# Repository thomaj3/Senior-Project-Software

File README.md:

This is the software for the Senior Project Curve Tracer utulizing PSoC

This curve tracer can handle enhancement mode NMOS and PMOS, as well as NPN and PNP BJTs

Value | Transistor Type | Range | Unit |
| --- | --- | --- | --- |
Id | N,P | [0, 20] | mA |
Ic | N,P | [0, 20] | mA |
Vd | N,P | [0, 9] | V |
Vc | N,P | [0, 9] | V |
Vg | N | [0, 4] | V |
Vg | P | [5, 9] | V |
Ib | N | [0 100] | uA |
Ib | P | [0 100] | uA |

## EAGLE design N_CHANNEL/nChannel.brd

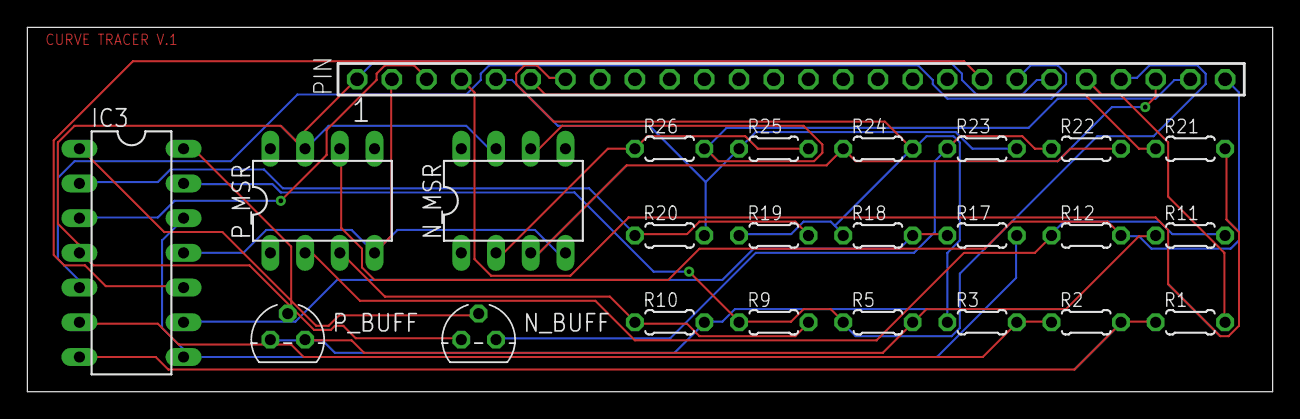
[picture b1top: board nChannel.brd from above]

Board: 2 copper layers, 91.1 x 26.7 mm, 24 parts (0 on the bottom side), 26 nets.

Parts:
IC3: MCP604P; DIL14
N_BUFF: TO92
N_MSR: AD711N; DIL08
PIN: SSW-126-02-G-S
P_BUFF: TO92
P_MSR: AD711N; DIL08
R1, R3, R18, R19: 10k; 0204/5
R2, R20: 20k; 0204/5
R5, R23: 52; 0204/5
R9, R10, R11, R12, R21, R22, R24, R25, R26: 100k; 0204/5
R17: 40k; 0204/5

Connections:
unnamed: PIN.7, PIN.24, P_BUFF.3, R3.1, R10.2, R18.1, R19.1, R24.2
unnamed: IC3.6, R2.1, R3.2
unnamed: IC3.3, PIN.3
unnamed: N_MSR.3, R22.2, R24.1
unnamed: N_MSR.2, R25.2, R26.1
unnamed: N_MSR.6, PIN.25, R26.2
unnamed: IC3.7, R1.1, R2.2
unnamed: IC3.9, R17.1, R18.2
unnamed: PIN.6, R21.1
unnamed: P_MSR.3, R9.2, R10.1
unnamed: P_MSR.2, R11.2, R12.1
unnamed: PIN.26, P_MSR.6, R12.2
unnamed: IC3.14, P_BUFF.2
unnamed: IC3.11, N_MSR.4, PIN.2, P_MSR.4
unnamed: IC3.1, N_BUFF.2
unnamed: IC3.2, R19.2, R20.1
unnamed: N_BUFF.1, R22.1, R23.1
unnamed: PIN.5, R20.2, R23.2, R25.1
unnamed: PIN.4, R21.2
unnamed: IC3.8, IC3.12, R17.2
unnamed: P_BUFF.1, R5.2, R11.1
unnamed: PIN.22, R1.2
unnamed: IC3.13, PIN.23, R5.1, R9.1
unnamed: IC3.4, N_BUFF.3, N_MSR.7, PIN.1, PIN.21, P_MSR.7
unnamed: IC3.5, PIN.20
unnamed: IC3.10, PIN.19

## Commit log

2018-10-20 First Commit for PSoC Firmware
2018-10-20 Updating File and Folder names for potential collaboration
2018-10-20 Removed duplicated directory
2018-10-20 Updating folder names, no substantial changes
2018-10-24 Switched PSoC Device from fat dev kit to prototyping kit
2018-10-27 Created dynamic Vgs test points based upon Vgs_th and error if Vgs_th find fails or is too hihg
2018-11-05 Updated Vgs_test_points method, will now use test points between Vth and max current draw of 20 mA
2018-11-28 Updating Comments
2019-02-02 added some header files for settings
2019-02-02 optimized search process, no more duplicate Vds arrays, created a test function for a single point rather than one whole
2019-02-02 Revert "optimized search process, no more duplicate Vds arrays, created a test function for a single point rather than one whole"
    This reverts commit 747243d6832611c9e19dfa424bf9963aa3618a9a.
2019-02-02 Fixe PSoC Creator not opening up project
2019-02-02 Added NPN, PMOS, PNP support
2019-02-06 Added ADC sleep and changes to code to validate hardware integration
2019-02-25 Integration with Screen
2019-02-25 Screen Integration
2019-02-25 removed obsolete code
2019-03-01 Added Advanced DSP Filtering (Averaging)
2019-03-06 Solved first plot point on lower averaging points and cleaned up main function
2019-03-06 test
2019-03-06 removed test file
2019-03-06 added Font.h
2019-03-06 Add through lowercase i in Font.h
2019-03-06 Added more to Font.h
2019-03-07 Font.h: Added more characters, replaced tab with spaces
2019-03-09 Partial font library added with ability to write Vgs next to curve
2019-03-11 Added draw_string function to font.c (untested)
2019-03-12 Finished/Fixed bugs in font library
2019-03-12 Added pins for touch inputs
2019-03-13 Added Y and X axis, fixed up some of the draw_string function, and changed some draw_number to draw_string commands
2019-03-13 Changed placement of axis numbers
2019-03-15 Added a consistent labeling of y-axis, Y and X axis now have labels appropriate for their respective transistor type. Got rid of inefficent long switch statemnts. Ib and Vg labels now have unit measu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
2019-03-15 fixed some bugs with printing Ib
2019-03-26 Added lowercase letters
2019-04-02 Fixing local machine dependant bugs
2019-04-02 Final PCB before testing
2019-04-02 Removed lowercase letters due to memory issues
2019-04-02 Added muxes for P device support
2019-04-07 Added SD Card Support
2019-04-08 Added more thorough comments and overwrite support
2019-04-14 Partial program implemented
2019-04-14 Added draw_button function and placeholder screen for options
2019-04-15 added buttons for options screen
2019-04-15 added option screens
2019-04-15 updated isr code.txt
2019-04-18 reworked options screen, added comments
2019-04-18 changed curve options screen, changed interrupt mode, added font scaling
2019-04-20 standardized return button for options, added average options screen
2019-04-20 fixed a bug that allowed the number of averages to go below 1
2019-04-22 bug fixes, enabled option settings to work
2019-04-22 replaced settling time option with draw grid option
2019-04-22 added comments
2019-04-22 added PIZZA TIME
2019-04-22 fixes for PIZZA TIME
2019-04-22 Added ADC Sleep commands directly to single test funcitons
2019-04-22 Pizza Time and testing fixes
2019-04-23 Added second options screen with cooldown time option
2019-04-23 Added max Vds option
2019-04-23 Added more colors for PIZZA TIME
2019-04-23 Multiple SD file support (99 files), the no cool down static grid, and variable drain voltage
2019-04-23 Stability fixes in changing Max Drain Voltage
2019-04-24 added home menu button, fixes for second option screen
2019-04-28 P-channel test fixes
2019-05-06 Integrated SD and Screen SPI
2019-05-06 fixed HEAD messages in code
2019-05-07 fixes for corrupted files
2019-05-07 more fixes for corrupted files
2019-05-07 added comments and code for SD debugging
